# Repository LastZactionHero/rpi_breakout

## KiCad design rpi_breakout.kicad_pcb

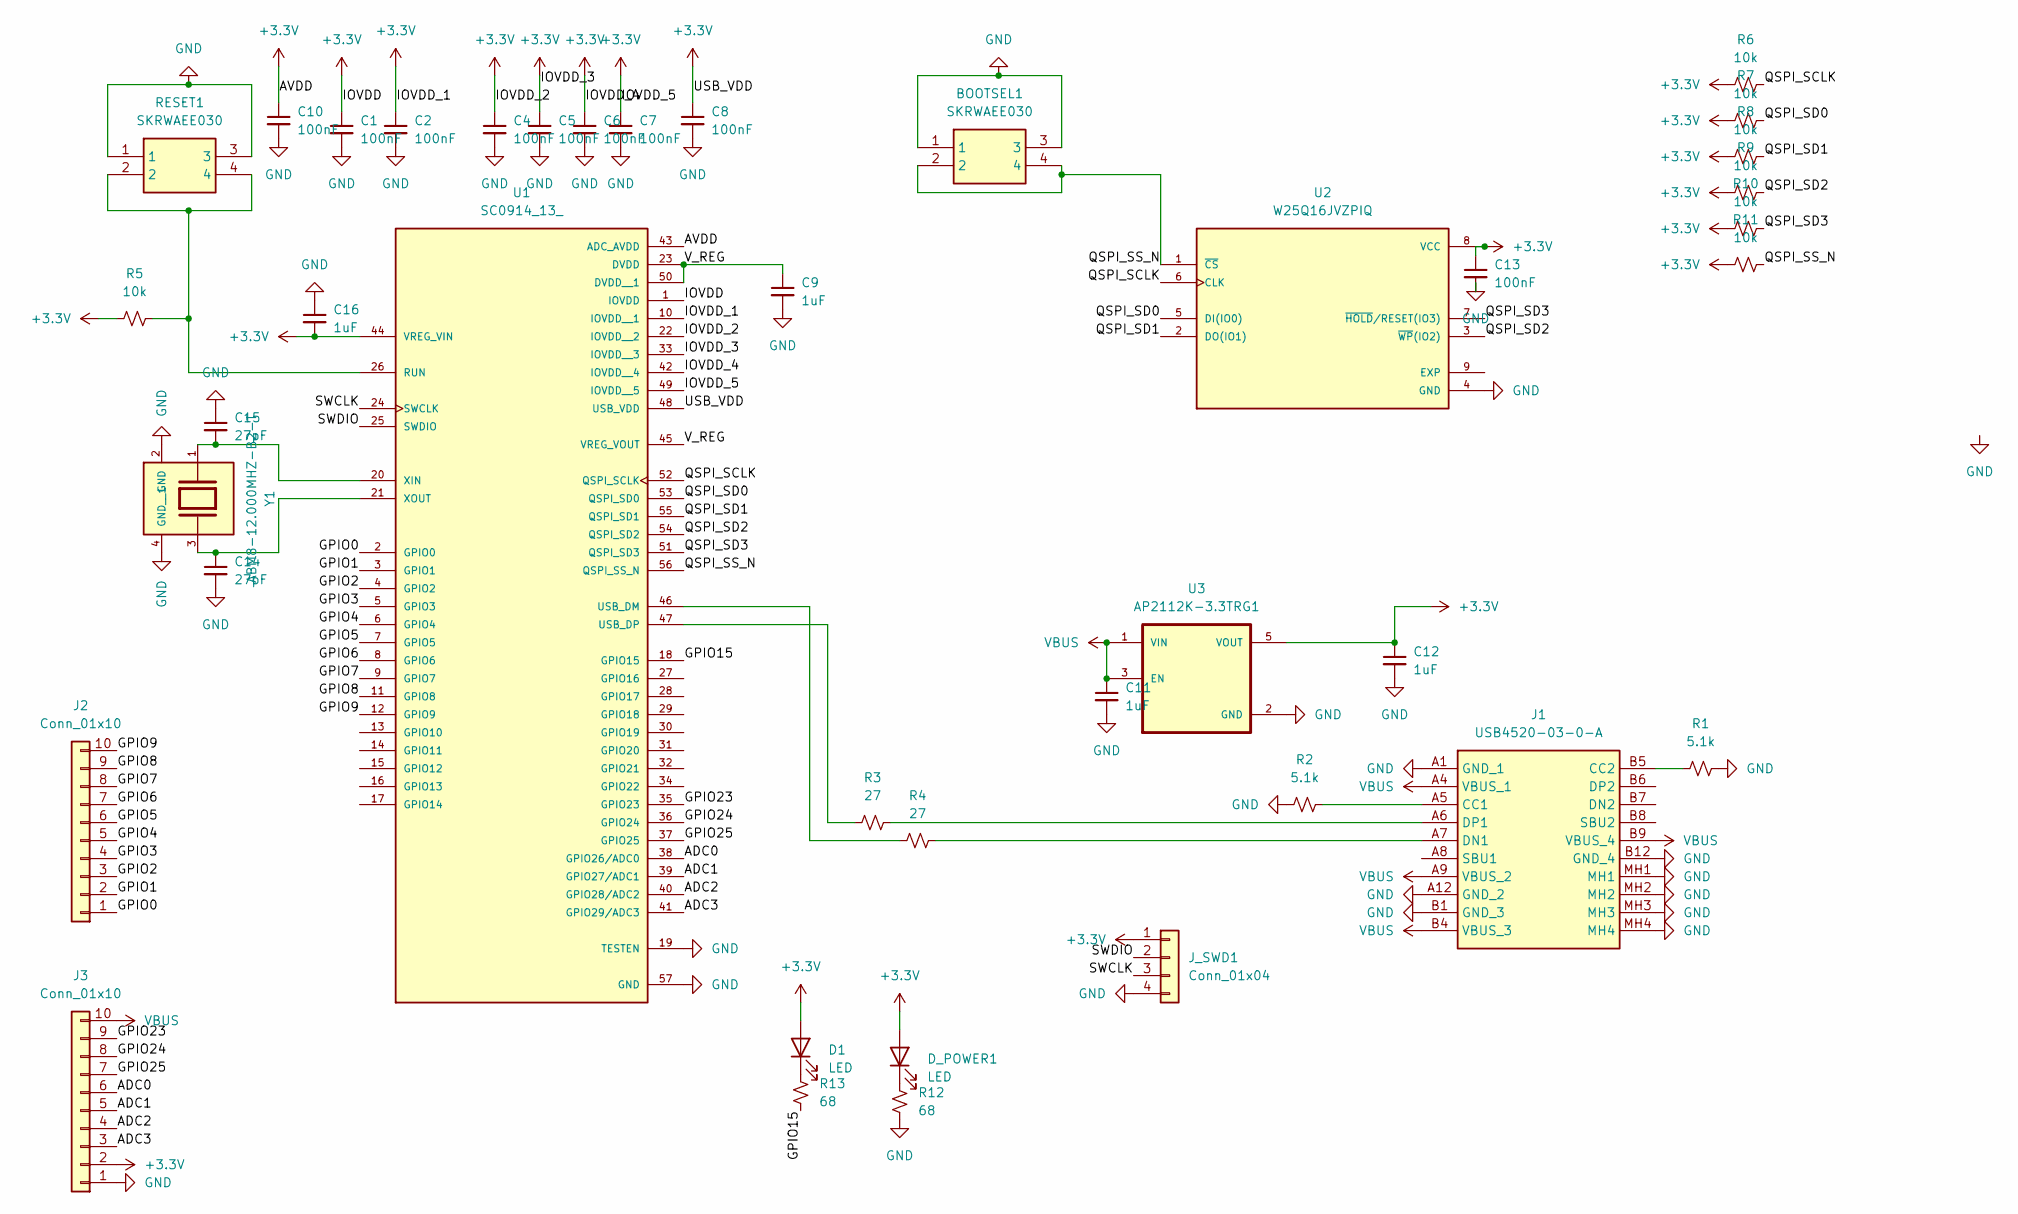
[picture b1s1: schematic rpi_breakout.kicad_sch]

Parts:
BOOTSEL1: SKRWAEE030; Mouser Part Number 688-SKRWAEE030
C1, C2, C4, C5, C6, C7, C8, C10, C13: 100nF; C_0402_1005Metric
C9, C11, C12, C16: 1uF; C_0402_1005Metric
C14, C15: 27pF; C_0402_1005Metric
D1: LED; LED_0805_2012Metric
D_POWER1: LED; LED_0805_2012Metric
J1: USB4520-03-0-A; USB4520030A; Manufacturer_Part_Number USB4520-03-0-A; Mouser Part Number 640-USB4520030A
J2, J3: Conn_01x10; PinHeader_1x10_P2.54mm_Vertical
J_SWD1: Conn_01x04; PinHeader_1x04_P2.54mm_Vertical
R1, R2: 5.1k; R_0402_1005Metric
R3, R4: 27; R_0402_1005Metric
R5, R6, R7, R8, R9, R10, R11: 10k; R_0402_1005Metric
R12, R13: 68; R_0402_1005Metric
RESET1: SKRWAEE030; Mouser Part Number 688-SKRWAEE030
U1: SC0914_13_; QFN40P700X700X90-57N; PARTREV 2.2
U2: W25Q16JVZPIQ; SON127P500X600X80-9N
U3: AP2112K-3.3TRG1; SOT95P285X140-5N; PARTREV 2-2
Y1: ABM8-12.000MHZ-B2-T; XTAL_ABM8-12.000MHZ-B2-T; PARTREV 44041

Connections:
+3.3V: C1.1, C2.1, C4.1, C5.1, C6.1, C7.1, C8.1, C10.1, C12.1, C13.1, C16.2, D1.2 (A), D_POWER1.2 (A), J3.2, J_SWD1.1, R5.1, R6.1, R7.1, R8.1, R9.1, R10.1, R11.1, U1.1 (IOVDD), U1.10 (IOVDD__1), U1.22 (IOVDD__2), U1.33 (IOVDD__3), U1.42 (IOVDD__4), U1.43 (ADC_AVDD), U1.44 (VREG_VIN), U1.48 (USB_VDD), U1.49 (IOVDD__5), U2.8 (VCC), U3.5 (VOUT)
/ADC0: J3.6, U1.38 (GPIO26/ADC0)
/ADC1: J3.5, U1.39 (GPIO27/ADC1)
/ADC2: J3.4, U1.40 (GPIO28/ADC2)
/ADC3: J3.3, U1.41 (GPIO29/ADC3)
/GPIO0: J2.1, U1.2 (GPIO0)
/GPIO1: J2.2, U1.3 (GPIO1)
/GPIO2: J2.3, U1.4 (GPIO2)
/GPIO3: J2.4, U1.5 (GPIO3)
/GPIO4: J2.5, U1.6 (GPIO4)
/GPIO5: J2.6, U1.7 (GPIO5)
/GPIO6: J2.7, U1.8 (GPIO6)
/GPIO7: J2.8, U1.9 (GPIO7)
/GPIO8: J2.9, U1.11 (GPIO8)
/GPIO9: J2.10, U1.12 (GPIO9)
/GPIO15: R13.2, U1.18 (GPIO15)
/GPIO23: J3.9, U1.35 (GPIO23)
/GPIO24: J3.8, U1.36 (GPIO24)
/GPIO25: J3.7, U1.37 (GPIO25)
/QSPI_SCLK: R6.2, U1.52 (QSPI_SCLK), U2.6 (CLK)
/QSPI_SD0: R7.2, U1.53 (QSPI_SD0), U2.5 (DI(IO0))
/QSPI_SD1: R8.2, U1.55 (QSPI_SD1), U2.2 (DO(IO1))
/QSPI_SD2: R9.2, U1.54 (QSPI_SD2), U2.3 (~WP(IO2))
/QSPI_SD3: R10.2, U1.51 (QSPI_SD3), U2.7 (~HOLD/RESET(IO3))
/QSPI_SS_N: BOOTSEL1.2, BOOTSEL1.4, R11.2, U1.56 (QSPI_SS_N), U2.1 (~CS)
/SWCLK: J_SWD1.3, U1.24 (SWCLK)
/SWDIO: J_SWD1.2, U1.25 (SWDIO)
/V_REG: C9.1, U1.23 (DVDD), U1.45 (VREG_VOUT), U1.50 (DVDD__1)
GND: BOOTSEL1.1, BOOTSEL1.3, C1.2, C2.2, C4.2, C5.2, C6.2, C7.2, C8.2, C9.2, C10.2, C11.2, C12.2, C13.2, C14.2, C15.1, C16.1, J1.A1 (GND_1), J1.A12 (GND_2), J1.B1 (GND_3), J1.B12 (GND_4), J1.MH1, J1.MH2, J1.MH3, J1.MH4, J3.1, J_SWD1.4, R1.2, R2.1, R12.2, RESET1.1, RESET1.3, U1.19 (TESTEN), U1.57 (GND), U2.4 (GND), U3.2 (GND), Y1.2 (GND), Y1.4 (GND__1)
unnamed: D1.1 (K), R13.1
unnamed: D_POWER1.1 (K), R12.1
unnamed: J1.A5 (CC1), R2.2
unnamed: J1.B5 (CC2), R1.1
unnamed: J1.A7 (DN1), R4.2
unnamed: J1.A6 (DP1), R3.2
unnamed: R5.2, RESET1.2, RESET1.4, U1.26 (RUN)
unnamed: R4.1, U1.46 (USB_DM)
unnamed: R3.1, U1.47 (USB_DP)
unnamed: C15.2, U1.20 (XIN), Y1.1
unnamed: C14.1, U1.21 (XOUT), Y1.3
VBUS: C11.1, J1.A4 (VBUS_1), J1.A9 (VBUS_2), J1.B4 (VBUS_3), J1.B9 (VBUS_4), J3.10, U3.1 (VIN), U3.3 (EN)

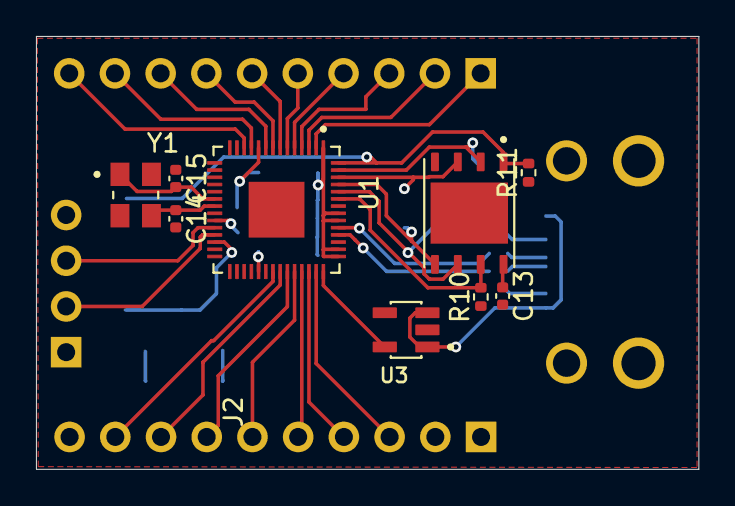
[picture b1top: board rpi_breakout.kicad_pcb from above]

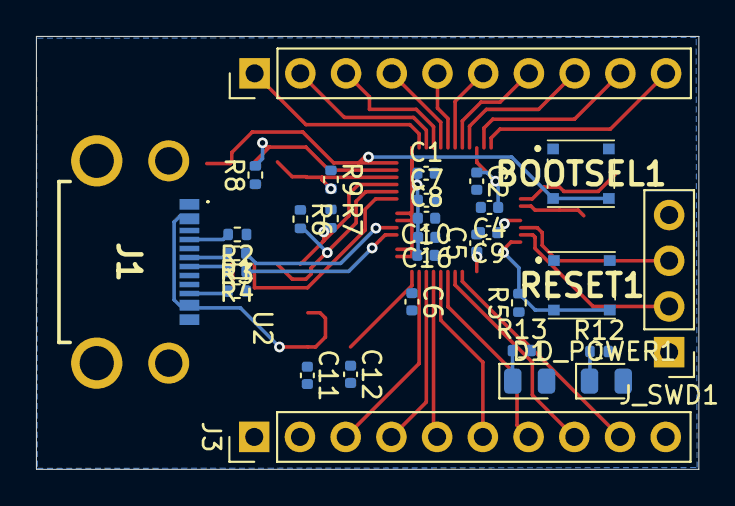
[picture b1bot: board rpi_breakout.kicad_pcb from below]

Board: 4 copper layers, 36.8 x 24.1 mm, 40 parts (31 on the bottom side), 41 nets.

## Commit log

2025-08-20 Schematic updates; Starting pcb
2025-08-21 Routing
